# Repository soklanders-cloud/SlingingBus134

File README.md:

REMOTE CONTROL
------------------------------------------------------
It is a nine key, one encoder remote controller for multiple things (in my case it is used for a survailance robot). It has nine keys in 3X3 pattern, each key have its own function placed as follows, the speed control can be done by rotatory encoder.

-----------------------------------------------------
PCB
-----------------------------------------------------
Here is my schematic PCB, i am using this design on the board;

picture of PCB editor,

I used Ki-cad to make pcb from start.

-----------------------------------------------------
CAD
-----------------------------------------------------

It is a basic box with soft cornor, and some decorations. Contains of Two 3D printed parts, top cover and bottom case.
Pinned with four screw, have a PCB in middle.

I used Fusion 360! to design the case.

------------------------------------------------------
Firmware overview
------------------------------------------------------

This is code of KMK firmware.
The keys send direction and mode commands, the rotary encoder controls robot speed, and the OLED shows the current mode and last action.
Everything works together like a compact robot remote controller with visual feedback.

-----------------------------------------------------
Challanges
-----------------------------------------------------

This is my first hackpad, I never made any PCB, nor a 3D case (or any 3D object using Fusion 360). I had to learn every thing from scrach used multiple tutorials, AI and google docs for documentation.
With my online classes it took more than a week to learn everything and every important tools.

-----------------------------------------------------
BOM
-----------------------------------------------------

Here is everything, you need to set this PCB:-

XIAO RP2040------1

MX Switches------9

1N4148 Diodes----9

EC11 Encoder-----1

0.91″ OLED-------1

Keycaps----------9

Top cover--------1

Bottom case------1

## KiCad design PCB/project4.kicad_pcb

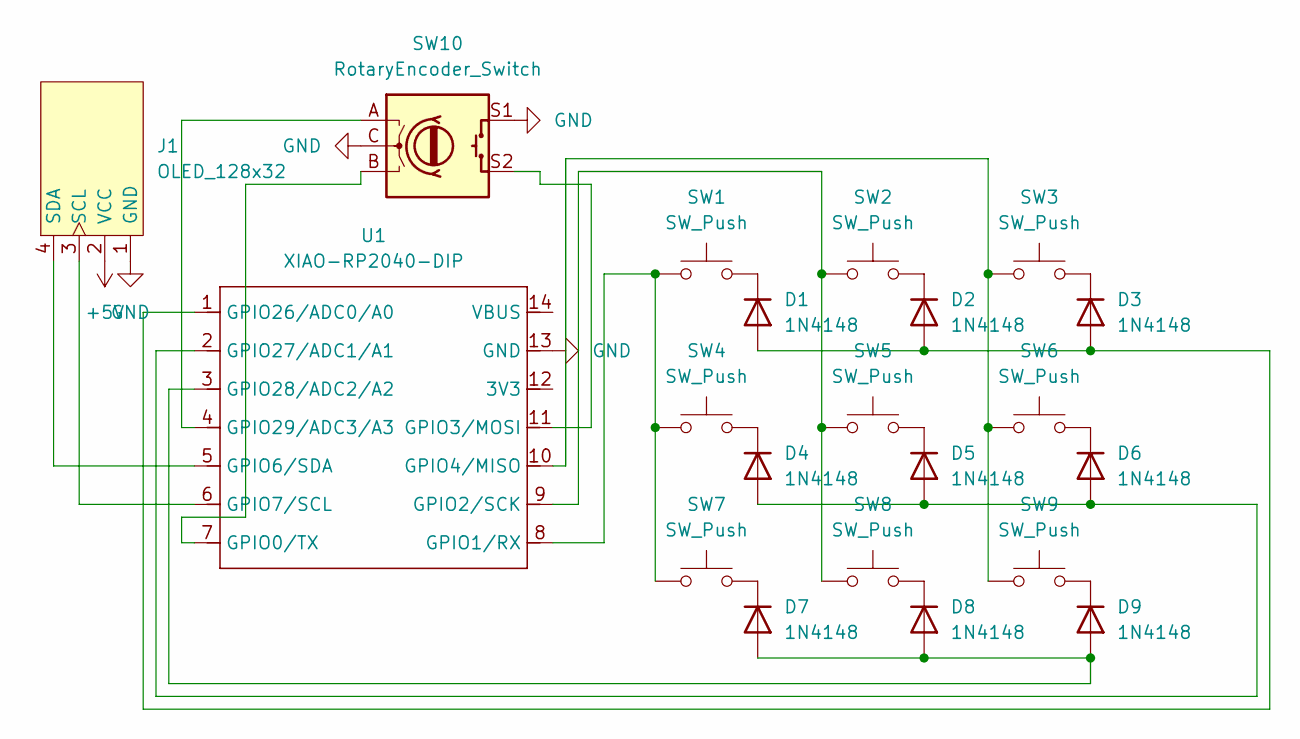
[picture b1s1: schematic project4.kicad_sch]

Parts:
D1, D2, D3, D4, D5, D6, D7, D8, D9: 1N4148; D_DO-35_SOD27_P7.62mm_Horizontal
J1: OLED_128x32; SSD1306-0.91-OLED-4pin-128x32
SW1, SW2, SW3, SW4, SW5, SW6, SW7, SW8, SW9: SW_Push; SW_Cherry_MX_1.00u_PCB
SW10: RotaryEncoder_Switch; RotaryEncoder_Alps_EC11E-Switch_Vertical_H20mm
U1: XIAO-RP2040-DIP

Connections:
+5V: J1.2 (VCC)
GND: J1.1 (GND), SW10.C, SW10.S1, U1.13 (GND)
unnamed: D1.2 (A), D2.2 (A), D3.2 (A), U1.1 (GPIO26/ADC0/A0)
unnamed: D1.1 (K), SW1.2
unnamed: D2.1 (K), SW2.2
unnamed: D3.1 (K), SW3.2
unnamed: D4.2 (A), D5.2 (A), D6.2 (A), U1.2 (GPIO27/ADC1/A1)
unnamed: D4.1 (K), SW4.2
unnamed: D5.1 (K), SW5.2
unnamed: D6.1 (K), SW6.2
unnamed: D7.2 (A), D8.2 (A), D9.2 (A), U1.3 (GPIO28/ADC2/A2)
unnamed: D7.1 (K), SW7.2
unnamed: D8.1 (K), SW8.2
unnamed: D9.1 (K), SW9.2
unnamed: J1.3 (SCL), U1.6 (GPIO7/SCL)
unnamed: J1.4 (SDA), U1.5 (GPIO6/SDA)
unnamed: SW10.B, U1.7 (GPIO0/TX)
unnamed: SW1.1, SW4.1, SW7.1, U1.8 (GPIO1/RX)
unnamed: SW2.1, SW5.1, SW8.1, U1.9 (GPIO2/SCK)
unnamed: SW10.S2, U1.11 (GPIO3/MOSI)
unnamed: SW3.1, SW6.1, SW9.1, U1.10 (GPIO4/MISO)
unnamed: SW10.A, U1.4 (GPIO29/ADC3/A3)

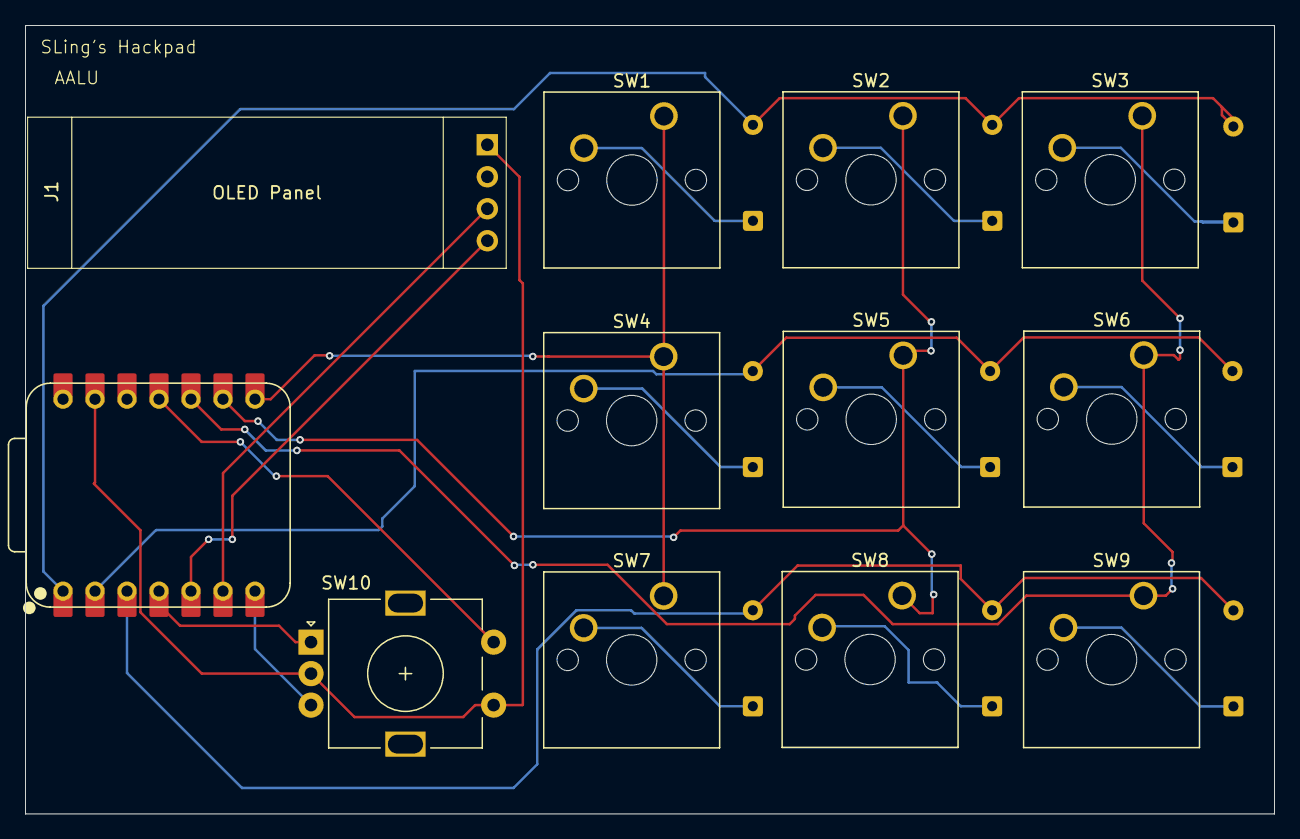
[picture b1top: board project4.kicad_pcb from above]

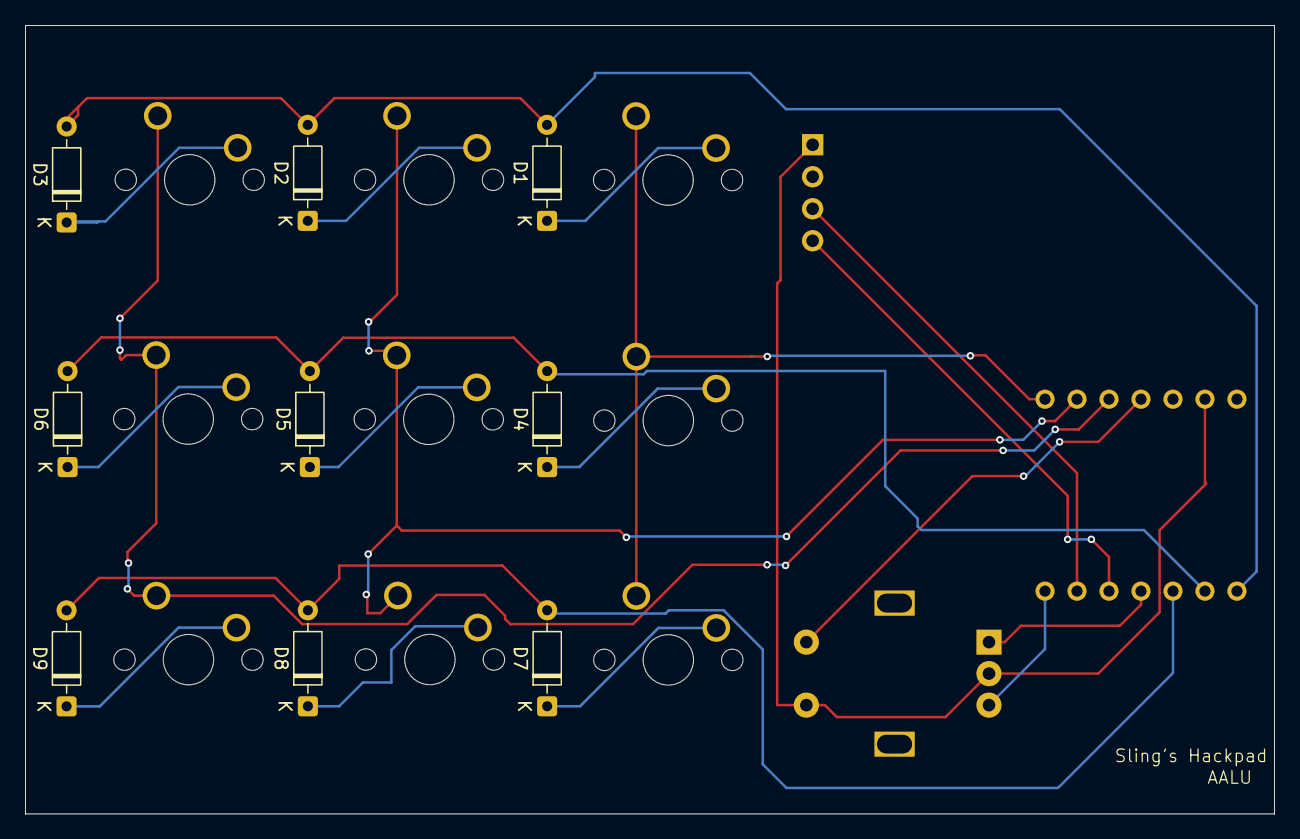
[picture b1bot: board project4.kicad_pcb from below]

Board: 2 copper layers, 99.2 x 62.6 mm, 21 parts (9 on the bottom side), 21 nets.

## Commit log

2025-12-28 Firmware
2025-12-28 main1
2025-12-29 Firm ware
